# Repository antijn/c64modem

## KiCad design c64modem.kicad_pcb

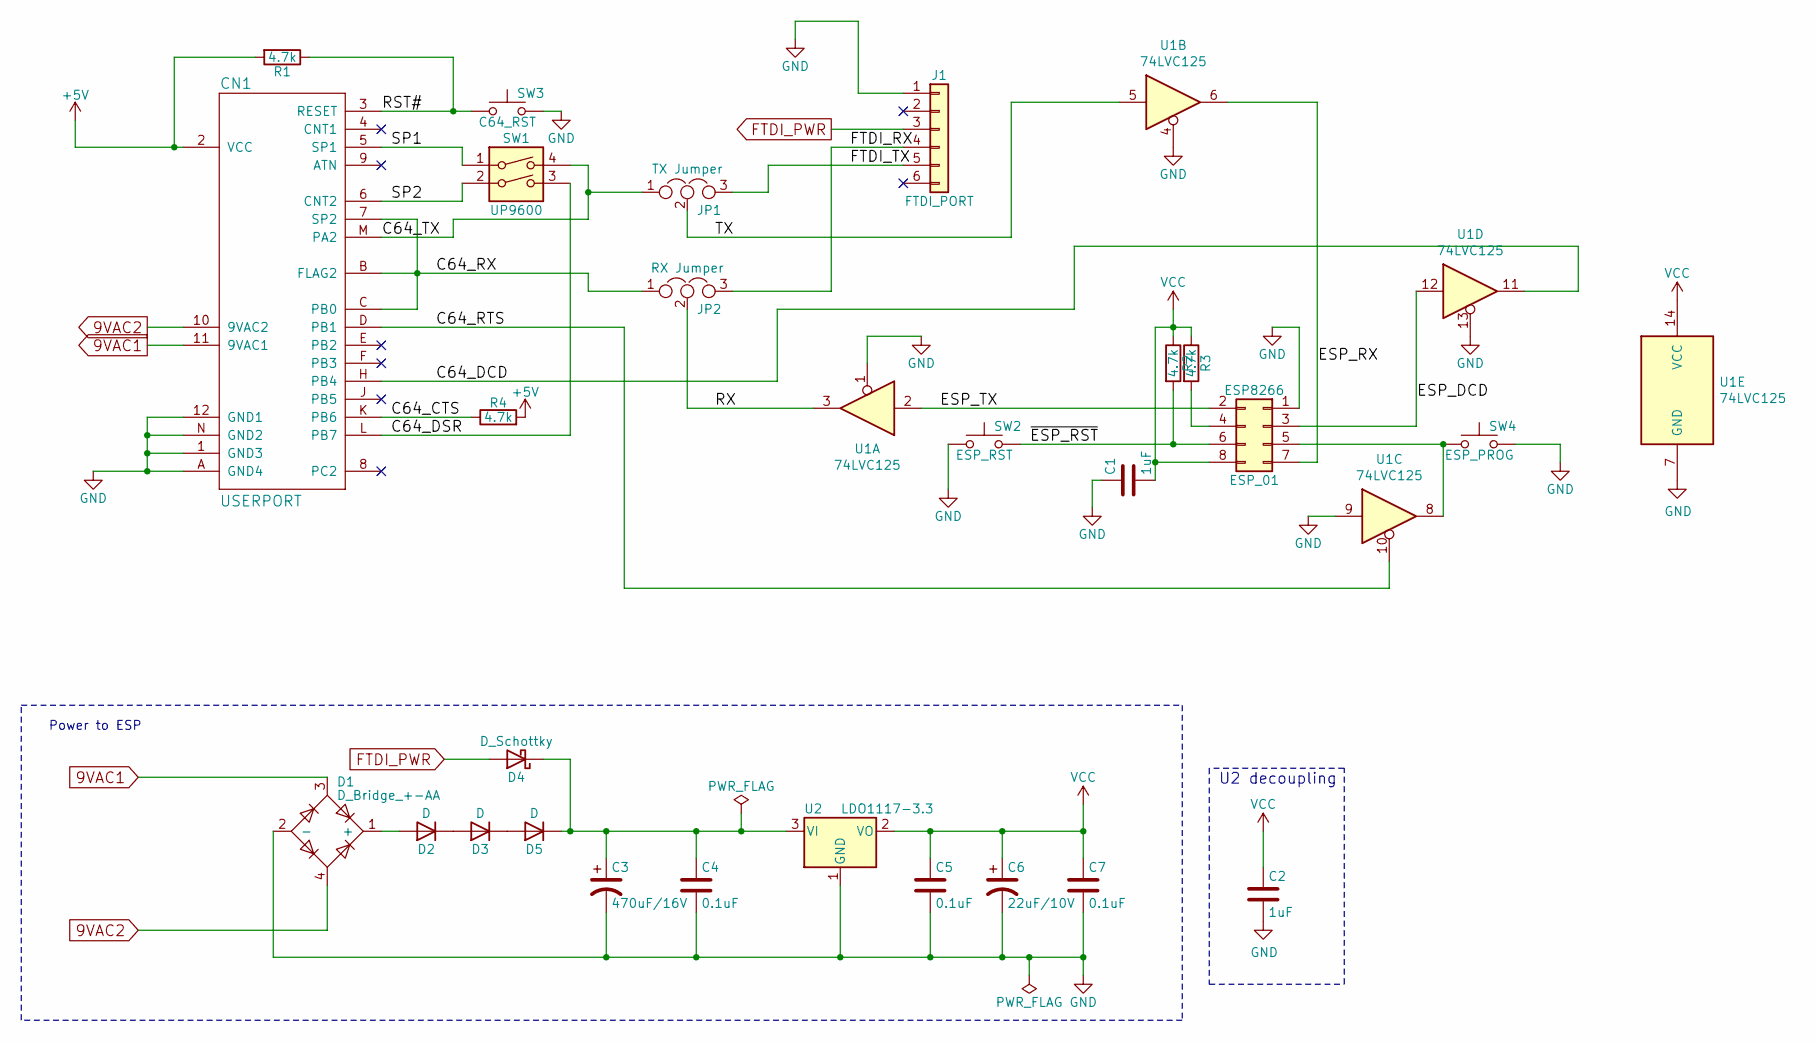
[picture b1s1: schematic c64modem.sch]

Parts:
C1, C2: 1uF; C_0805_2012Metric_Pad1.15x1.40mm_HandSolder
C3: 470uF/16V; CP_Radial_D10.0mm_P5.00mm
C4, C5, C7: 0.1uF; C_0805_2012Metric_Pad1.15x1.40mm_HandSolder
C6: 22uF/10V; CP_Radial_D5.0mm_P2.00mm
CN1: USERPORT
D1: D_Bridge_+-AA; DIP-4_W7.62mm_LongPads
D2, D3, D5: D; D_DO-34_SOD68_P2.54mm_Vertical_AnodeUp
D4: D_Schottky; D_SOD-323
ESP8266: ESP_01; PinSocket_2x04_P2.54mm_Vertical
J1: FTDI_PORT; PinHeader_1x06_P2.54mm_Vertical
JP1: TX Jumper; PinHeader_1x03_P2.54mm_Vertical
JP2: RX Jumper; PinHeader_1x03_P2.54mm_Vertical
R1, R2, R3, R4: 4.7k; R_0805_2012Metric_Pad1.15x1.40mm_HandSolder
SW1: UP9600; SW_DIP_SPSTx02_Slide_9.78x7.26mm_W7.62mm_P2.54mm
SW2: ESP_RST; SW_PUSH_6mm_H5mm
SW3: C64_RST; SW_PUSH_6mm_H5mm
SW4: ESP_PROG; SW_PUSH_6mm_H5mm
U1: 74LVC125; TSSOP-14_4.4x5mm_P0.65mm
U2: LDO1117-3.3; SOT-223-3_TabPin2

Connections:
9VAC1: CN1.11 (9VAC1), D1.3
9VAC2: CN1.10 (9VAC2), D1.4
+5V: CN1.2 (VCC), R1.2, R4.2
/C64_CTS: CN1.K (PB6), R4.1
/C64_DCD: CN1.H (PB4), U1.11
/C64_DSR: CN1.L (PB7), SW1.3
/C64_RTS: CN1.D (PB1), U1.10
/C64_RX: CN1.7 (SP2), CN1.B (FLAG2), CN1.C (PB0), JP2.1
/C64_TX: CN1.M (PA2), JP1.1, SW1.4
/ESP_DCD: ESP8266.3, U1.12
/ESP_RX: ESP8266.7, U1.6
/ESP_TX: ESP8266.2, U1.2
/FTDI_RX: J1.4, JP2.3
/FTDI_TX: J1.5, JP1.3
/RST#: CN1.3 (RESET), R1.1, SW3.1
/RX: JP2.2, U1.3
/SP1: CN1.5 (SP1), SW1.1
/SP2: CN1.6 (CNT2), SW1.2
/TX: JP1.2, U1.5
/~ESP_RST: ESP8266.6, R2.2, SW2.2
FTDI_PWR: D4.2 (A), J1.3
GND: C1.1, C2.2, C3.2, C4.2, C5.2, C6.2, C7.2, CN1.1 (GND3), CN1.12 (GND1), CN1.A (GND4), CN1.N (GND2), D1.2 (-), ESP8266.1, J1.1, SW2.1, SW3.2, SW4.2, U1.1, U1.4, U1.7 (GND), U1.9, U1.13, U2.1 (GND)
unnamed: C3.1, C4.1, D4.1 (K), D5.1 (K), U2.3 (VI)
unnamed: D1.1 (+), D2.2 (A)
unnamed: D2.1 (K), D3.2 (A)
unnamed: D3.1 (K), D5.2 (A)
unnamed: ESP8266.4, R3.2
unnamed: ESP8266.5, SW4.1, U1.8
VCC: C1.2, C2.1, C5.1, C6.1, C7.1, ESP8266.8, R2.1, R3.1, U1.14 (VCC), U2.2 (VO)

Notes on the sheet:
Power to ESP
U2 decoupling

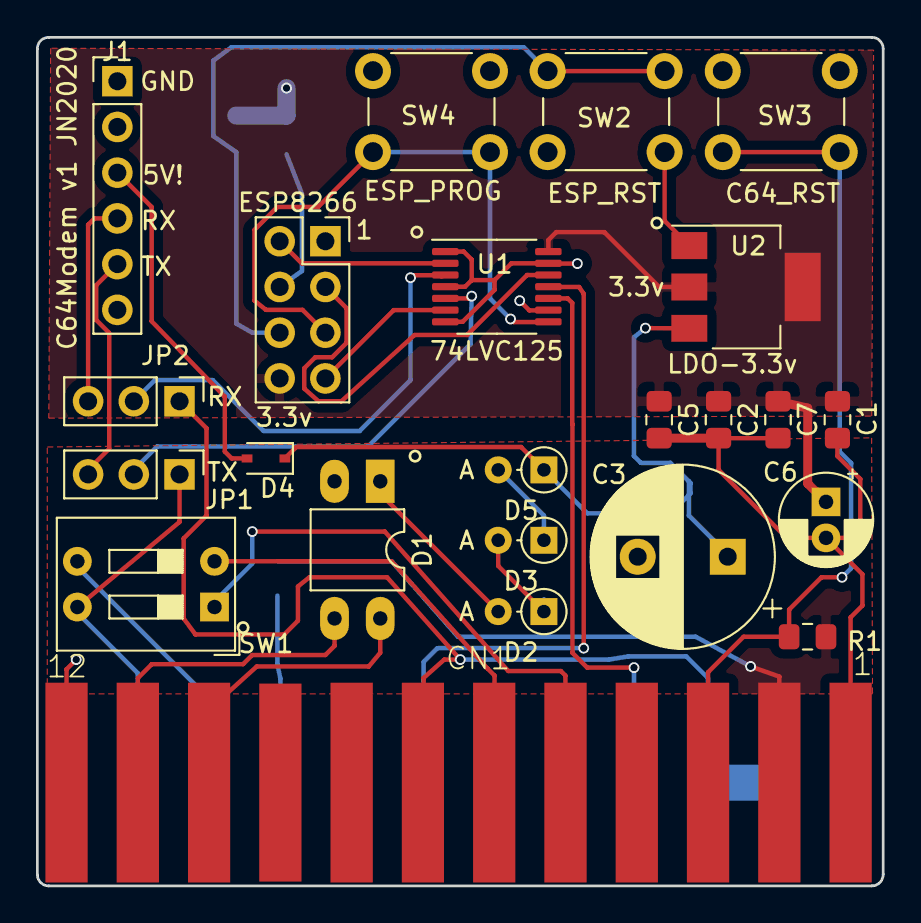
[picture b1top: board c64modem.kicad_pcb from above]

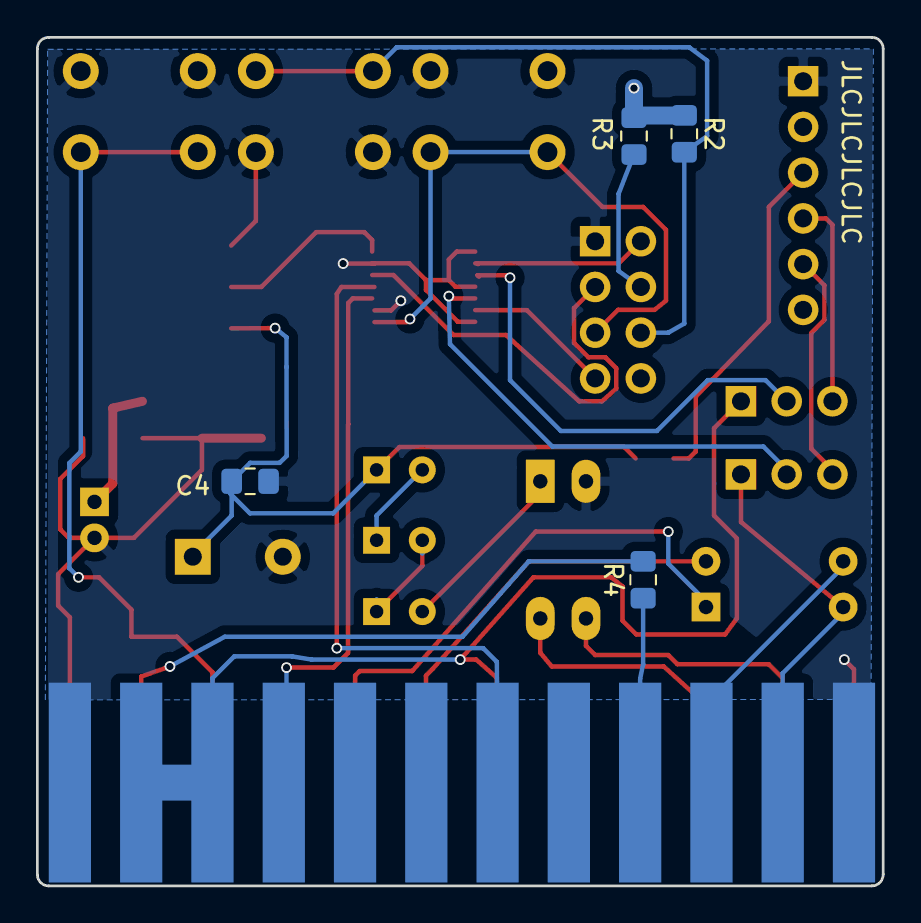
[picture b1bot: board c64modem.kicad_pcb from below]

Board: 2 copper layers, 47.0 x 47.1 mm, 27 parts (4 on the bottom side), 29 nets.

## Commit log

2018-04-09 First revision
2020-09-03 Reroute
2020-09-03 Fixed esp8266 header, routing
2020-09-05 Rework.
2023-11-24 Rework & add BOM
